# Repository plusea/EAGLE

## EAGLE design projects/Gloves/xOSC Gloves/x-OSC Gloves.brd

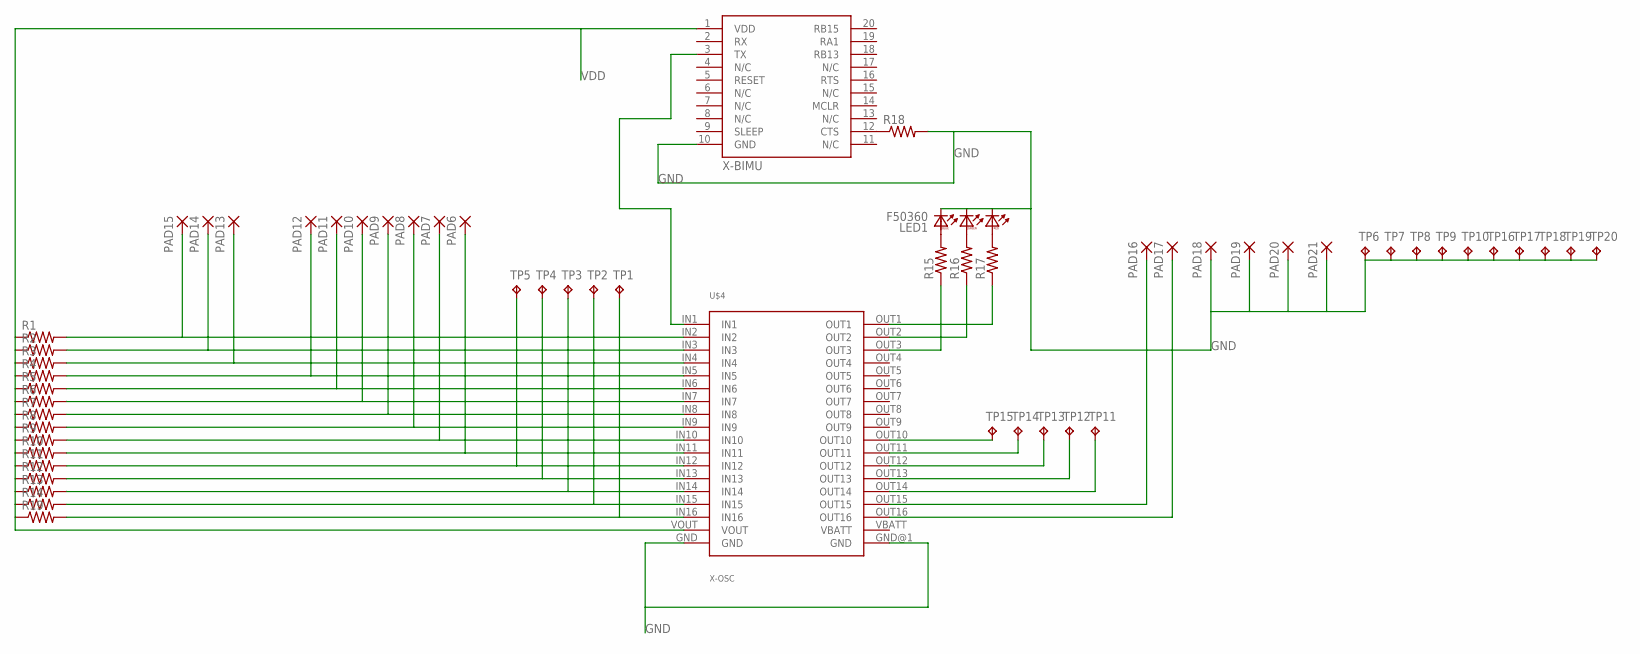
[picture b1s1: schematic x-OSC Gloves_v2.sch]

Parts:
LED1: F50360
PAD6, PAD7, PAD8, PAD9, PAD10, PAD11, PAD12, PAD13, PAD14, PAD15, PAD16, PAD17, PAD18, PAD19, PAD20, PAD21: 3,81/1,4
R1, R2, R3, R4, R5, R6, R7, R8, R9, R10, R11, R12, R13, R14, R15, R16, R17, R18, R19: RESISTOR0805-RES; 0805
TP1, TP2, TP3, TP4, TP5, TP6, TP7, TP8, TP9, TP10, TP11, TP12, TP13, TP14, TP15, TP16, TP17, TP18, TP19, TP20: TPTP20R; TP20R
U$4: X-OSC; X-OSC_SMD
U$5: X-BIMU; X-BIMU_SMD

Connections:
GND: LED1.BC, LED1.GC, LED1.RC, PAD18.1, PAD19.1, PAD20.1, PAD21.1, R18.2, TP6.TP, TP7.TP, TP8.TP, TP9.TP, TP10.TP, TP16.TP, TP17.TP, TP18.TP, TP19.TP, TP20.TP, U$4.GND, U$4.GND@1 (GND), U$5.10 (GND)
unnamed: LED1.BA, R15.2
unnamed: LED1.GA, R16.2
unnamed: R15.1, U$4.OUT3
unnamed: PAD15.1, R1.2, U$4.IN2
unnamed: R16.1, U$4.OUT2
unnamed: PAD14.1, R2.2, U$4.IN3
unnamed: PAD13.1, R3.2, U$4.IN4
unnamed: PAD12.1, R4.2, U$4.IN5
unnamed: PAD11.1, R5.2, U$4.IN6
unnamed: R18.1, U$5.12 (CTS)
unnamed: U$4.IN1, U$5.3 (TX)
unnamed: PAD10.1, R6.2, U$4.IN7
unnamed: PAD9.1, R7.2, U$4.IN8
unnamed: PAD8.1, R8.2, U$4.IN9
unnamed: PAD7.1, R9.2, U$4.IN10
unnamed: PAD6.1, R10.2, U$4.IN11
unnamed: LED1.RA, R17.2
unnamed: R11.2, TP5.TP, U$4.IN12
unnamed: R12.2, TP4.TP, U$4.IN13
unnamed: R13.2, TP3.TP, U$4.IN14
unnamed: R14.2, TP2.TP, U$4.IN15
unnamed: R19.2, TP1.TP, U$4.IN16
unnamed: PAD16.1, U$4.OUT15
unnamed: PAD17.1, U$4.OUT16
unnamed: R17.1, U$4.OUT1
unnamed: TP11.TP, U$4.OUT14
unnamed: TP12.TP, U$4.OUT13
unnamed: TP13.TP, U$4.OUT12
unnamed: TP14.TP, U$4.OUT11
unnamed: TP15.TP, U$4.OUT10
VDD: R1.1, R2.1, R3.1, R4.1, R5.1, R6.1, R7.1, R8.1, R9.1, R10.1, R11.1, R12.1, R13.1, R14.1, R19.1, U$4.VOUT, U$5.1 (VDD)

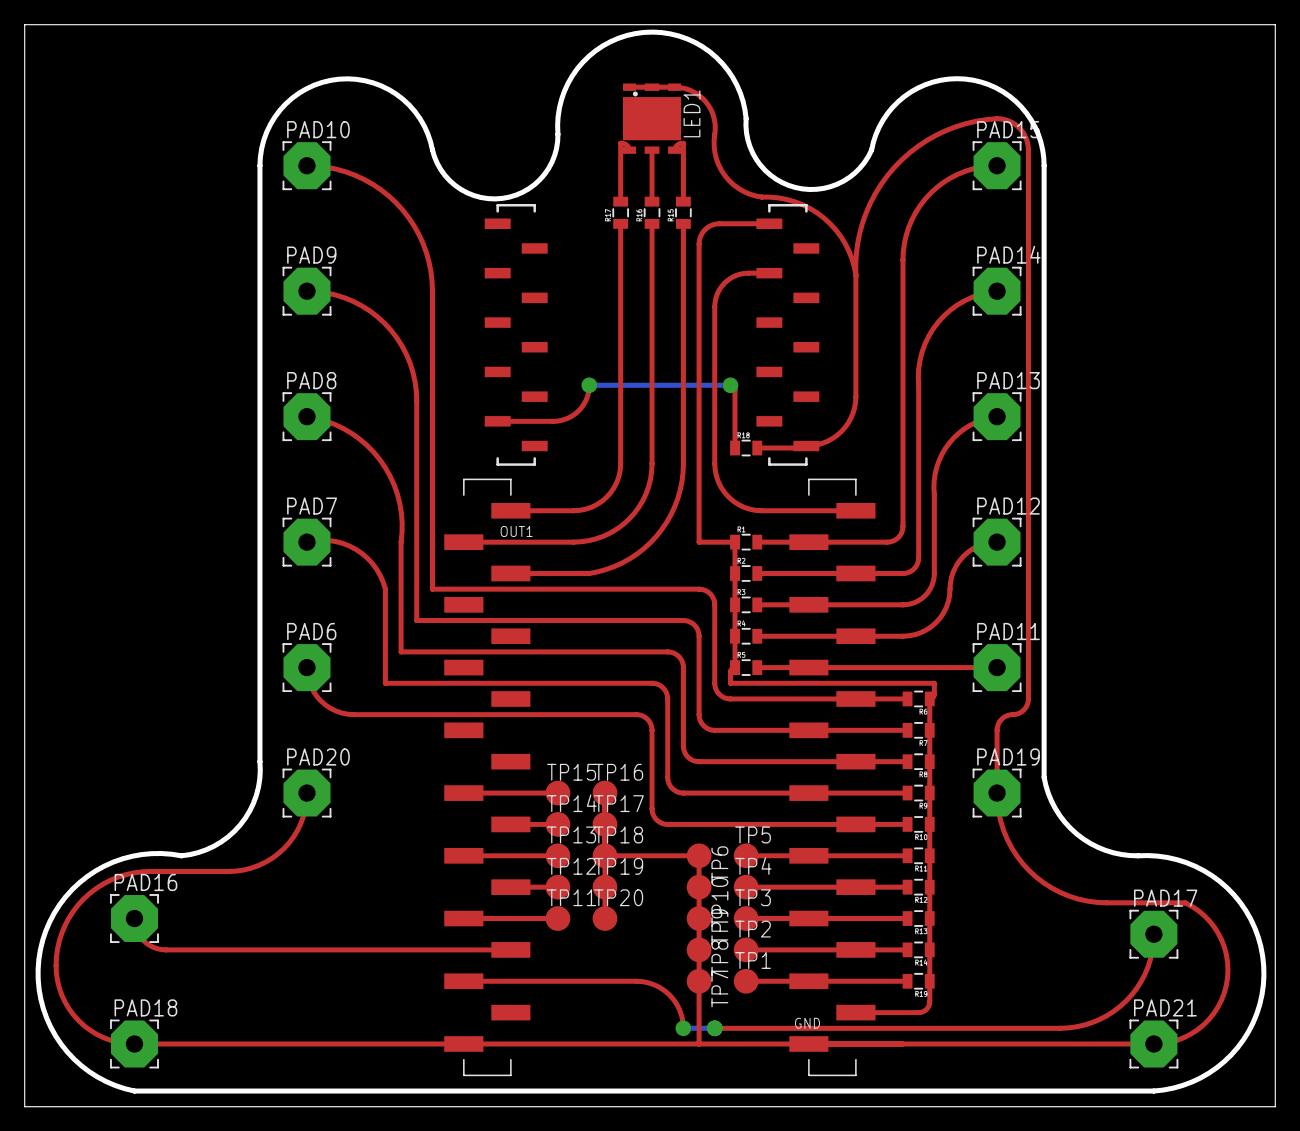
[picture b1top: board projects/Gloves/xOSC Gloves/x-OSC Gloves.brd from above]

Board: 2 copper layers, 101.3 x 87.6 mm, 58 parts (0 on the bottom side), 32 nets.

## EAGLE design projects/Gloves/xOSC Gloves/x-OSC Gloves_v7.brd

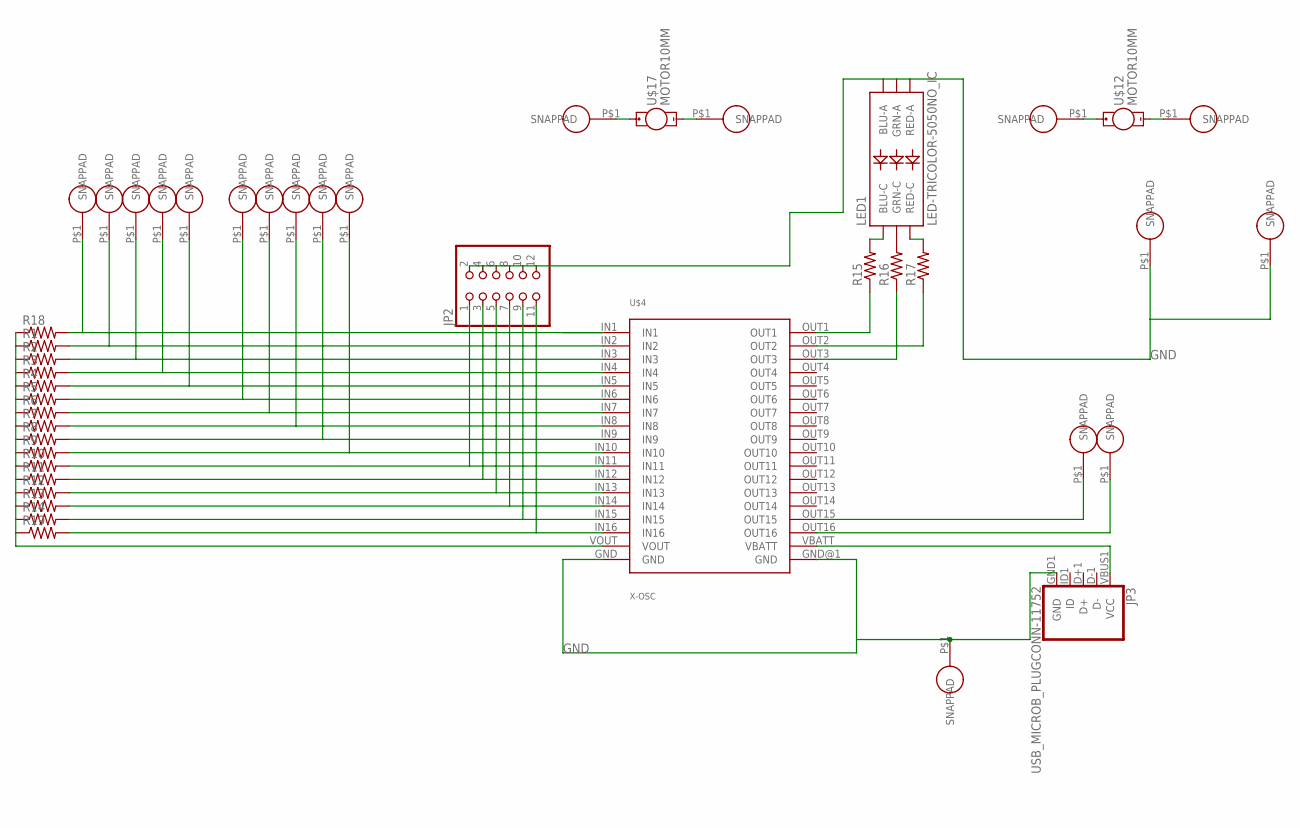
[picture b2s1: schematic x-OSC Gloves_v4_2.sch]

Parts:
JP2: PINHD-2X6/90; 2X06/90
JP3: USB_MICROB_PLUGCONN-11752; USB-B-MICRO-SMD_V03
LED1: LED-TRICOLOR-5050NO_IC; LED-TRICOLOR-5050
R1, R2, R3, R4, R5, R6, R7, R8, R9, R10, R11, R12, R13, R14, R15, R16, R17, R18, R19: RESISTOR0805-RES; 0805
U$1, U$2, U$3, U$6, U$7, U$8, U$9, U$10, U$11, U$13, U$14, U$15, U$16, U$18, U$19, U$20, U$21, U$22, U$23: SNAP-PAD_7MM_ROUND; SNAP-PAD_7MM_RD
U$4: X-OSC; X-OSC_SMD
U$12, U$17: MOTOR10MM; VIBE-MOTOR-10MM

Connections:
GND: JP2.2, JP2.4, JP2.6, JP2.8, JP2.10, JP2.12, JP3.GND1 (GND), LED1.1 (GRN-A), LED1.2 (RED-A), LED1.3 (BLU-A), U$4.GND, U$4.GND@1 (GND), U$15.P$1, U$16.P$1, U$18.P$1
unnamed: LED1.6 (GRN-C), R16.2
unnamed: LED1.4 (BLU-C), R15.2
unnamed: R16.1, U$4.OUT3
unnamed: R1.2, U$1.P$1, U$4.IN2
unnamed: R2.2, U$2.P$1, U$4.IN3
unnamed: R3.2, U$3.P$1, U$4.IN4
unnamed: R4.2, U$4.IN5, U$6.P$1
unnamed: R5.2, U$4.IN6, U$7.P$1
unnamed: R6.2, U$4.IN7, U$8.P$1
unnamed: R7.2, U$4.IN8, U$9.P$1
unnamed: R8.2, U$4.IN9, U$10.P$1
unnamed: R9.2, U$4.IN10, U$11.P$1
unnamed: JP2.1, R10.2, U$4.IN11
unnamed: LED1.5 (RED-C), R17.2
unnamed: JP2.3, R11.2, U$4.IN12
unnamed: JP2.5, R12.2, U$4.IN13
unnamed: JP2.7, R13.2, U$4.IN14
unnamed: JP2.9, R14.2, U$4.IN15
unnamed: JP2.11, R19.2, U$4.IN16
unnamed: U$4.OUT15, U$13.P$1
unnamed: U$4.OUT16, U$14.P$1
unnamed: R17.1, U$4.OUT2
unnamed: R15.1, U$4.OUT1
unnamed: U$12.+, U$22.P$1
unnamed: U$12.-, U$23.P$1
unnamed: JP3.VBUS1 (VCC), U$4.VBATT
unnamed: U$17.+, U$19.P$1
unnamed: R18.2, U$4.IN1, U$21.P$1
unnamed: U$17.-, U$20.P$1
unnamed: R1.1, R2.1, R3.1, R4.1, R5.1, R6.1, R7.1, R8.1, R9.1, R10.1, R11.1, R12.1, R13.1, R14.1, R18.1, R19.1, U$4.VOUT

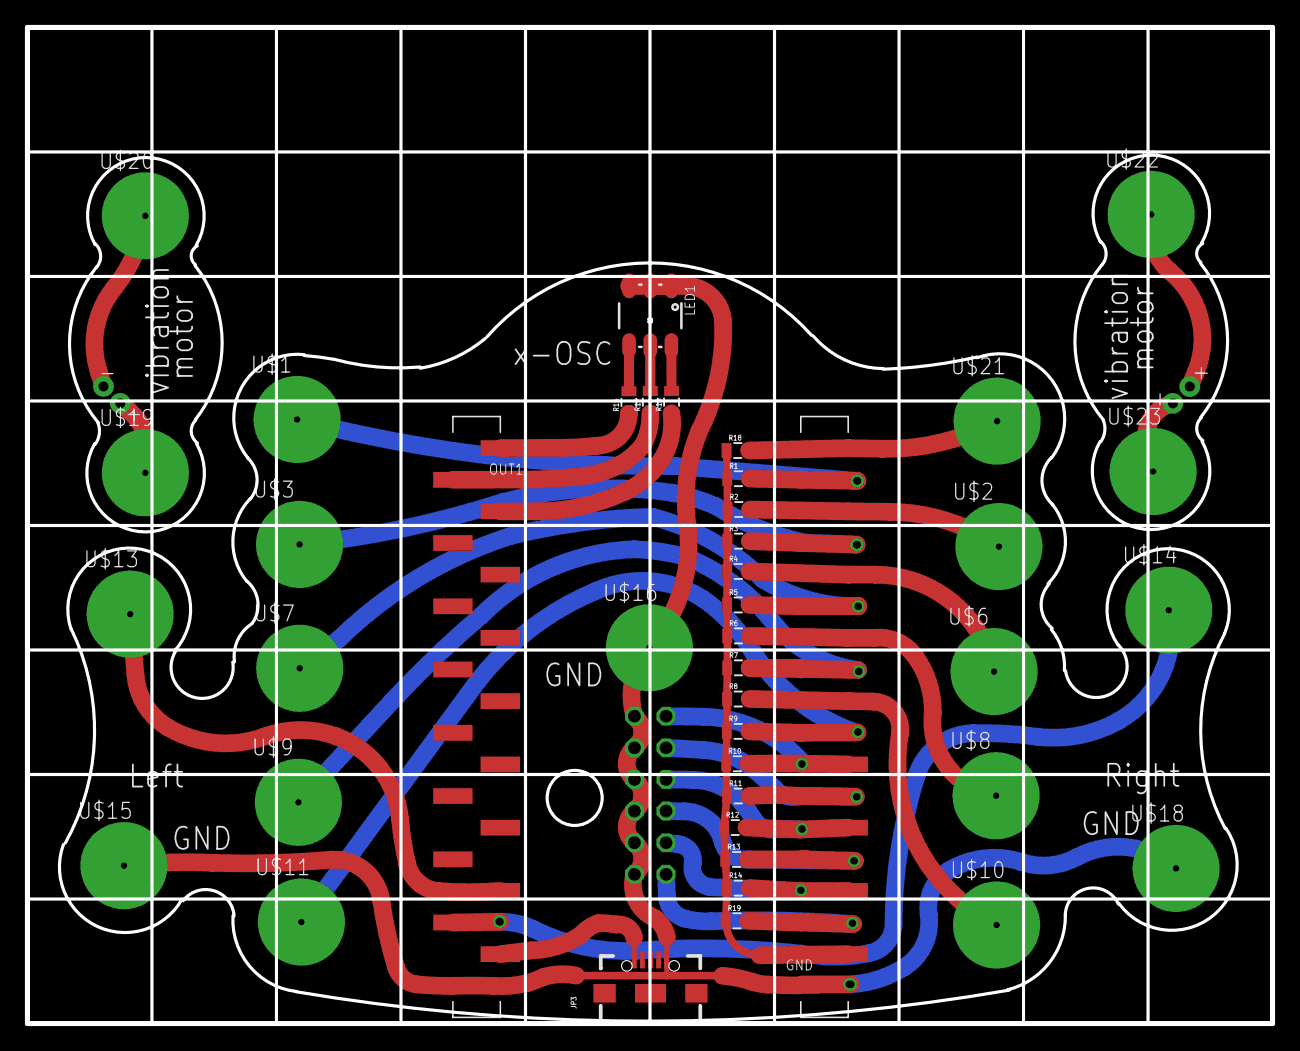
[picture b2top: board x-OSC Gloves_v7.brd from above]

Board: 2 copper layers, 100.0 x 80.0 mm, 44 parts (1 on the bottom side), 31 nets.

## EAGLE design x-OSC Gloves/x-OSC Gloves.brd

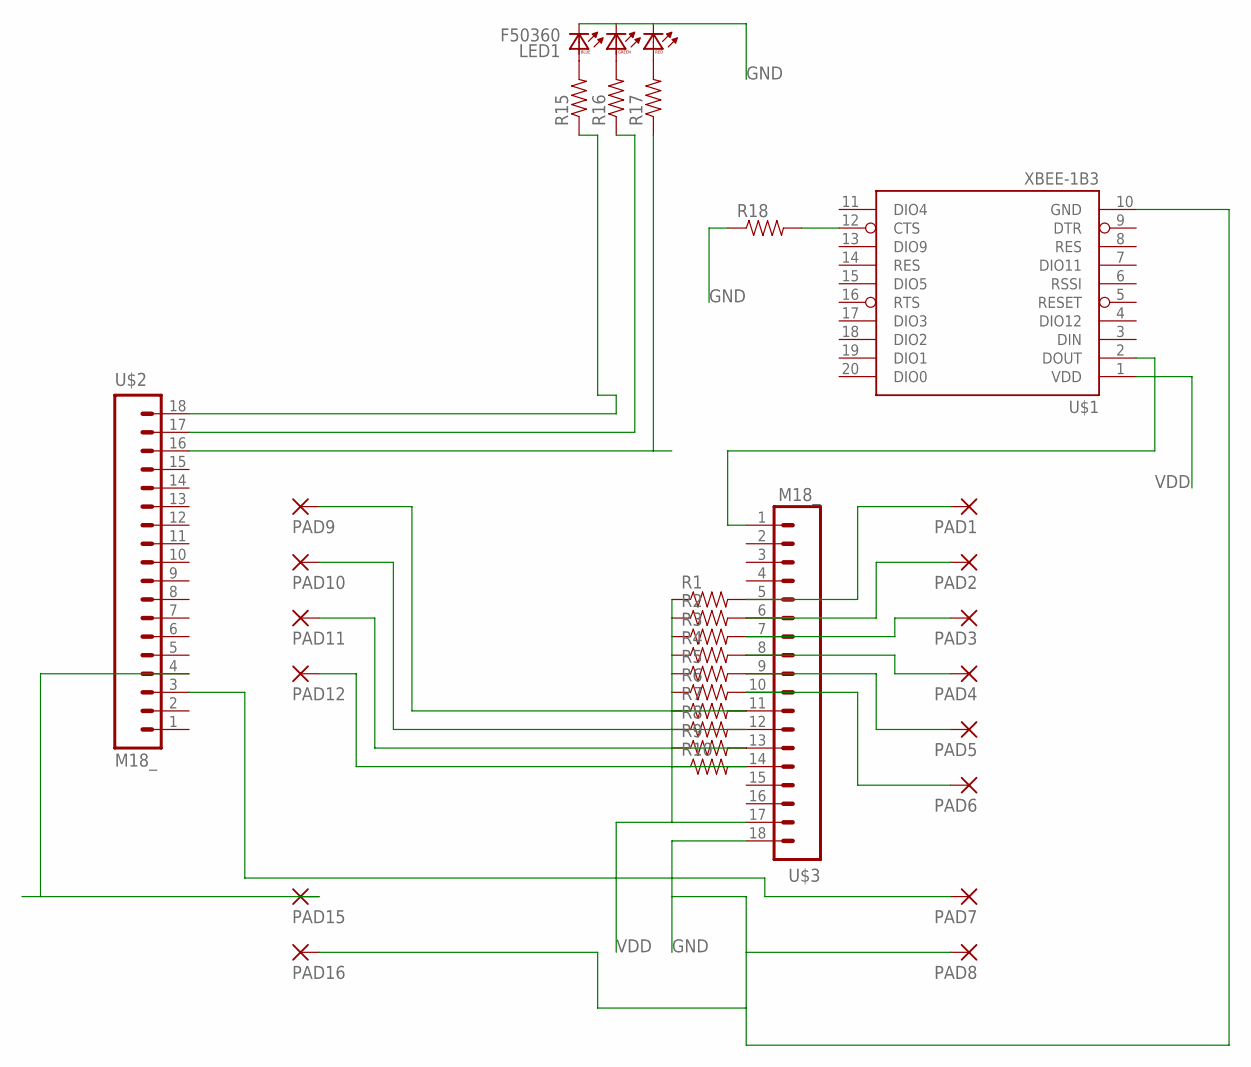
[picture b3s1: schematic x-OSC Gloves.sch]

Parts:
LED1: F50360
PAD1, PAD2, PAD3, PAD4, PAD5, PAD6, PAD7, PAD8, PAD9, PAD10, PAD11, PAD12, PAD15, PAD16: 3,81/1,4
R1, R2, R3, R4, R5, R6, R7, R8, R9, R10, R15, R16, R17, R18: RESISTOR0805-RES; 0805
U$1: XBEE-1B3; XBEE-SMD
U$2, U$3: M18_; 1X18

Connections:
GND: LED1.BC, LED1.GC, LED1.RC, PAD8.1, PAD16.1, R18.1, U$1.10 (GND), U$3.18
unnamed: LED1.BA, R15.2
unnamed: LED1.GA, R16.2
unnamed: PAD3.1, R3.2, U$3.7
unnamed: PAD4.1, R4.2, U$3.8
unnamed: PAD5.1, R5.2, U$3.9
unnamed: PAD6.1, R6.2, U$3.10
unnamed: PAD9.1, R7.2, U$3.11
unnamed: PAD10.1, R8.2, U$3.12
unnamed: PAD11.1, R9.2, U$3.13
unnamed: R17.1, U$2.16
unnamed: PAD2.1, R2.2, U$3.6
unnamed: R18.2, U$1.12 (CTS)
unnamed: PAD7.1, U$2.3
unnamed: PAD15.1, U$2.4
unnamed: LED1.RA, R17.2
unnamed: R15.1, U$2.18
unnamed: R16.1, U$2.17
unnamed: PAD12.1, R10.2, U$3.14
unnamed: PAD1.1, R1.2, U$3.5
unnamed: U$1.2 (DOUT), U$3.1
VDD: R1.1, R2.1, R3.1, R4.1, R5.1, R6.1, R7.1, R8.1, R9.1, R10.1, U$1.1 (VDD), U$3.17

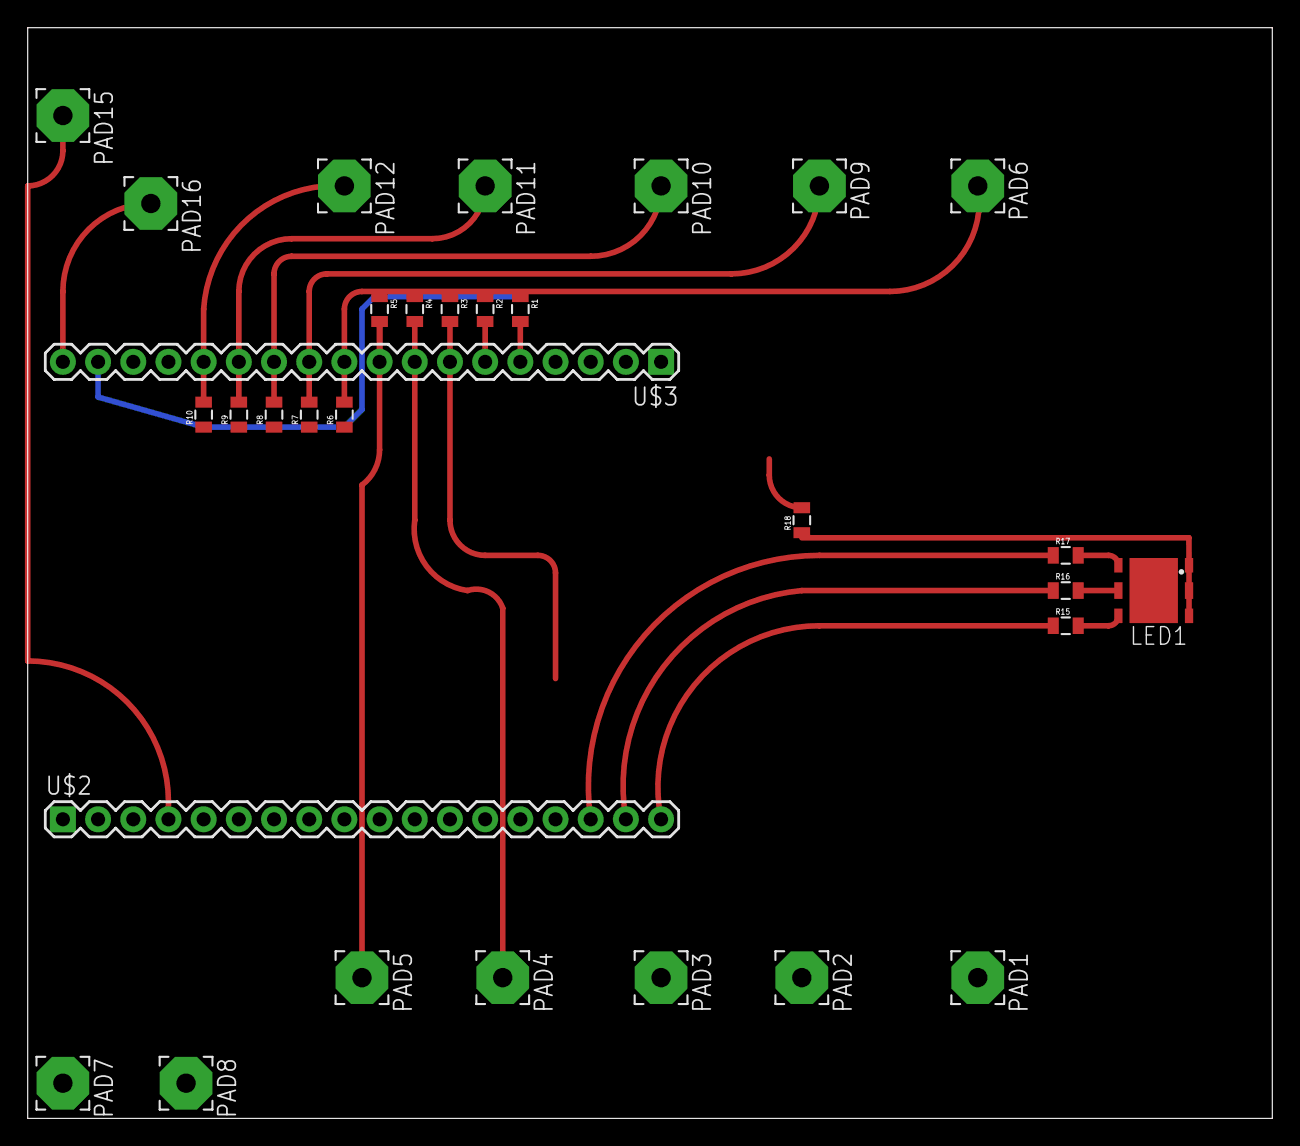
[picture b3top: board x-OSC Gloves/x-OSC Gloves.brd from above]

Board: 2 copper layers, 89.8 x 78.7 mm, 32 parts (1 on the bottom side), 22 nets.

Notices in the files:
parts and their libraries:
SparkFun-Passives: Licensing: CC v3.0 Share-Alike You are welcome to use this library for commercial purposes.
